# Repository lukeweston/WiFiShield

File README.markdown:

CC3000 Arduino-compatible 802.11b/g Wi-Fi shield   

Board must be fabbed with 1.6mm thick FR4 (although the microstrip impedence is not a strong function of board thickness), 2-layer 1 oz. Cu, with soldermask on both sides,
so that the 50-ohm coplanar waveguide has an impedence in the right ballpark.   
   
Preview image:   

Readme to be done later.

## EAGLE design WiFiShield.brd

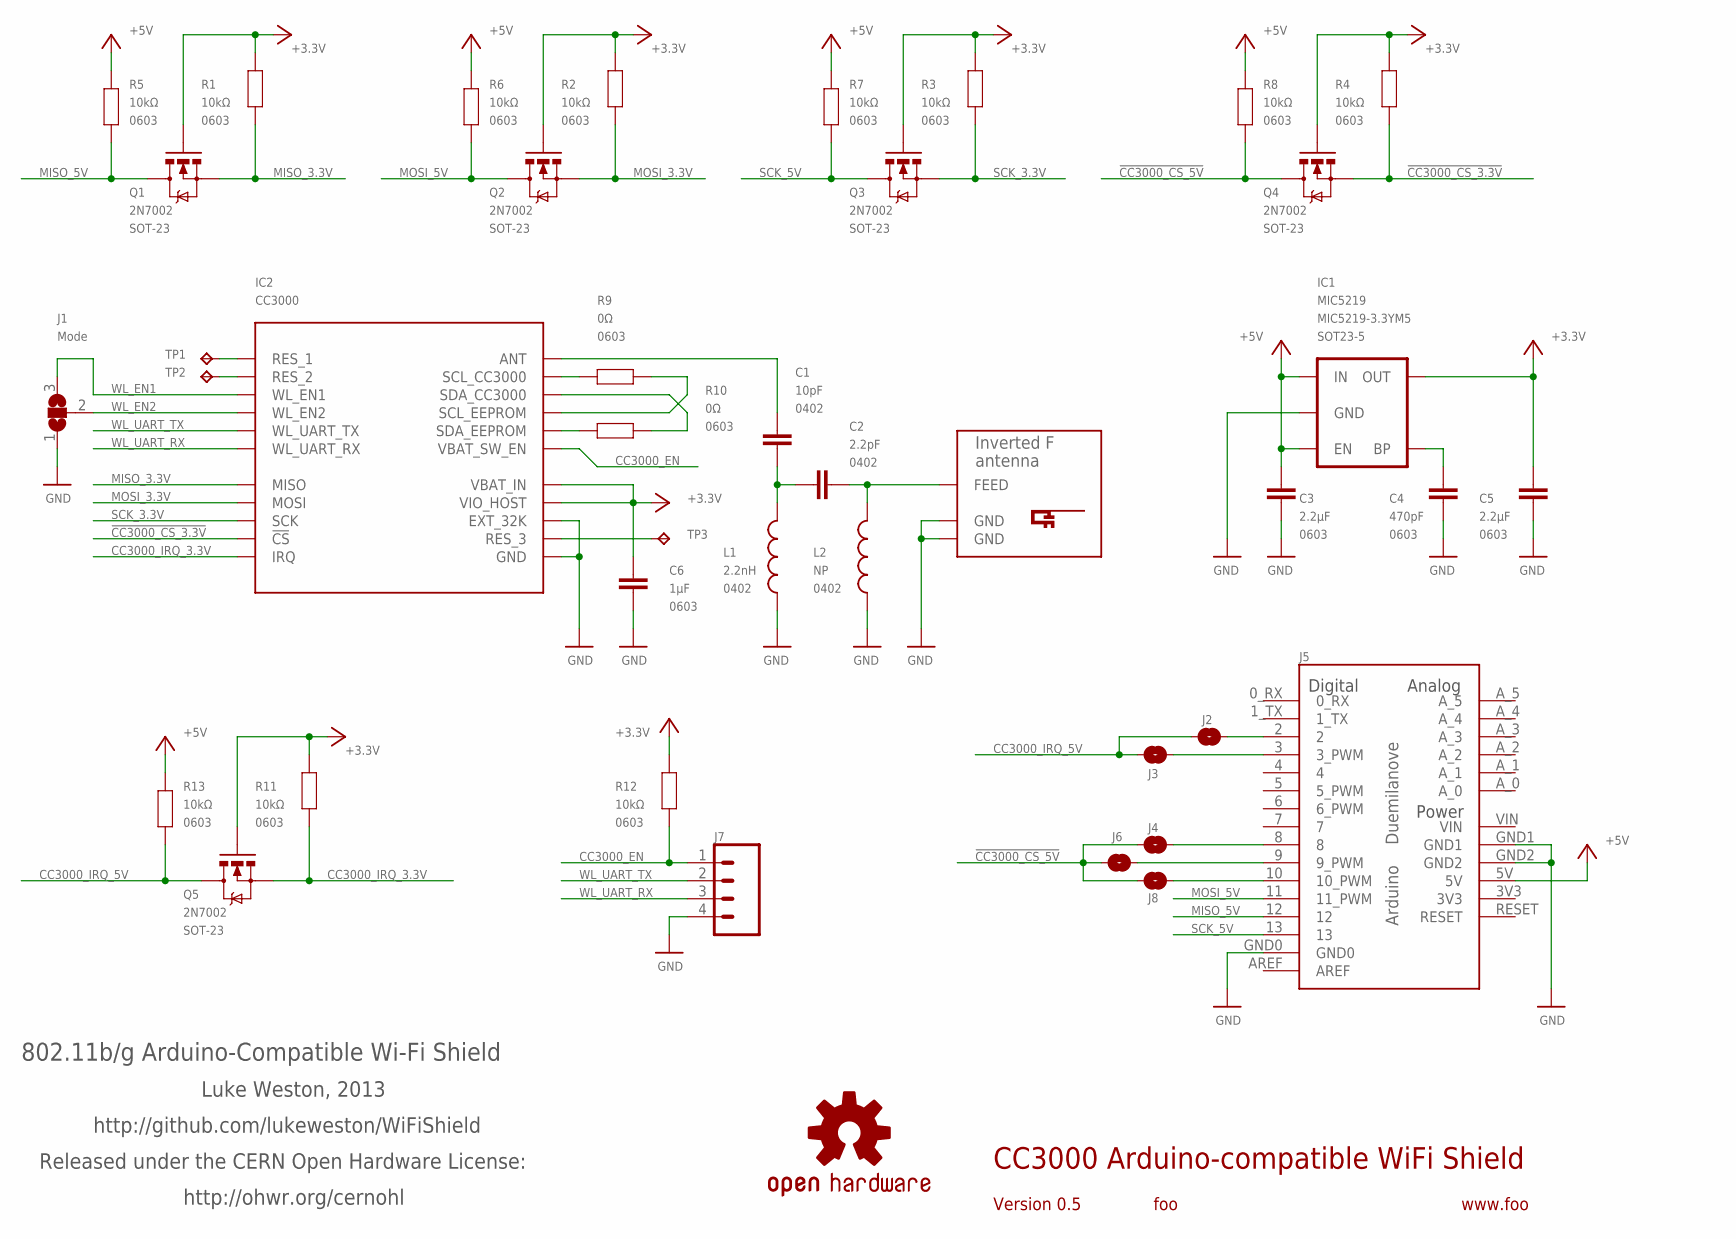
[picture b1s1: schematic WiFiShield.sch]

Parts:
A1: INVERTED_F_ANTENNA+2; DN007+2
C1: 10pF; C0402
C2: 2.2pF; C0402
C3, C5: 2.2µF; 0603
C4: 470pF; 0603
C6: 1µF; 0603
IC1: MIC5219; SOT23-5
IC2: CC3000
J1: Mode; SJ_2
J2, J3, J4, J6, J8: SJ
J5: Arduino-compatible headers; NO-OUTLINE-OCTAGONAL-NOTEXT
J7: M041.27MM; 1X04-1.27MM
L1: 2.2nH; C0402
L2: NP; C0402
Q1, Q2, Q3, Q4, Q5: 2N7002; SOT23-3
R1, R2, R3, R4, R5, R6, R7, R8, R11, R12, R13: 10kΩ; 0603
R9, R10: 0Ω; 0603
SY: OSHW-LOGOS; OSHW-LOGO-S
TP1, TP2, TP3: TPTP06R; TP06R

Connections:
3V3: J5.3V3
!CC3000_CS_3.3V: IC2.12 (!CS), Q4.2 (S), R4.1
!CC3000_CS_5V: J4.1, J6.1, J8.1, Q4.3 (D), R8.1
+3V3: C5.1, C6.2, IC1.5 (OUT), IC2.19 (VBAT_IN), IC2.23 (VIO_HOST), Q1.1 (G), Q2.1 (G), Q3.1 (G), Q4.1 (G), Q5.1 (G), R1.2, R2.2, R3.2, R4.2, R11.2, R12.2
+5V: C3.2, IC1.1 (IN), IC1.3 (EN), J5.5V, R5.2, R6.2, R7.2, R8.2, R13.2
CC3000_EN: IC2.26 (VBAT_SW_EN), J7.1, R12.1
CC3000_IRQ_3.3V: IC2.14 (IRQ), Q5.2 (S), R11.1
CC3000_IRQ_5V: J2.1, J3.1, Q5.3 (D), R13.1
GND: A1.GND, A1.GND@1 (GND), C3.1, C4.1, C5.2, C6.1, IC1.2 (GND), IC2.1 (GND), IC2.9 (GND), IC2.10 (GND), IC2.11 (GND), IC2.16 (GND), IC2.18 (GND), IC2.20 (GND), IC2.21 (EXT_32K), IC2.22 (GND), IC2.25 (GND), IC2.31 (GND), IC2.32 (GND), IC2.33 (GND), IC2.34 (GND), IC2.36 (GND), IC2.37 (GND), IC2.38 (GND), IC2.39 (GND), IC2.40 (GND), IC2.41 (GND), IC2.42 (GND), IC2.43 (GND), IC2.44 (GND), IC2.45 (GND), IC2.46 (GND), J1.1, J5.GND0, J5.GND1, J5.GND2, J7.4, L1.2, L2.2
MISO_3.3V: IC2.13 (MISO), Q1.2 (S), R1.1
MISO_5V: J5.12, Q1.3 (D), R5.1
MOSI_3.3V: IC2.15 (MOSI), Q2.2 (S), R2.1
MOSI_5V: J5.11 (11_PWM), Q2.3 (D), R6.1
unnamed: IC2.27 (SDA_EEPROM), R10.2
unnamed: IC2.28 (SDA_CC3000), R10.1
unnamed: J3.2, J5.3 (3_PWM)
unnamed: IC2.29 (SCL_EEPROM), R9.1
unnamed: J2.2, J5.2
unnamed: J5.9 (9_PWM), J6.2
unnamed: J4.2, J5.8
unnamed: J5.10 (10_PWM), J8.2
unnamed: IC2.30 (SCL_CC3000), R9.2
unnamed: C1.2, IC2.35 (ANT)
unnamed: C4.2, IC1.4 (BP)
unnamed: C1.1, C2.2, L1.1
unnamed: A1.FEED, C2.1, L2.1
RES_1: IC2.2 (RES_1), TP1.TP
RES_2: IC2.4 (RES_2), TP2.TP
RES_3: IC2.24 (RES_3), TP3.TP
SCK_3.3V: IC2.17 (SCK), Q3.2 (S), R3.1
SCK_5V: J5.13, Q3.3 (D), R7.1
VIN: J5.VIN
WL_EN1: IC2.7 (WL_EN1), J1.3
WL_EN2: IC2.5 (WL_EN2), J1.2
WL_UART_RX: IC2.8 (WL_UART_RX), J7.3
WL_UART_TX: IC2.6 (WL_UART_TX), J7.2

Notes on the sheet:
CC3000 Arduino-compatible WiFi Shield
Version 0.5
foo
www.foo
802.11b/g Arduino-Compatible Wi-Fi Shield
Luke Weston, 2013
http://github.com/lukeweston/WiFiShield
Released under the CERN Open Hardware License:
http://ohwr.org/cernohl

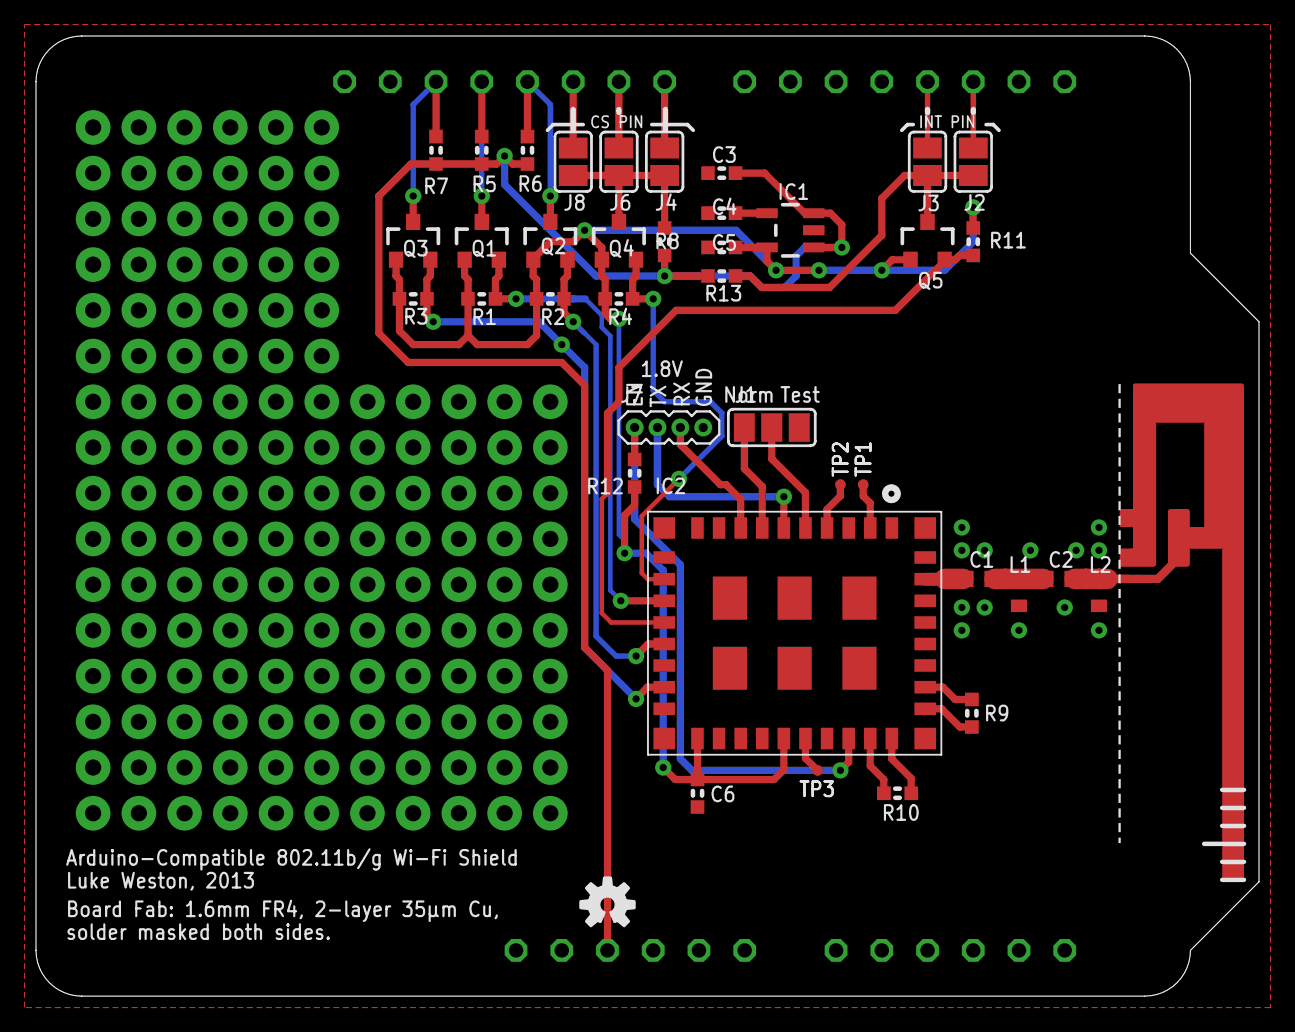
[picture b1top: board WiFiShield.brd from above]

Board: 2 copper layers, 67.9 x 53.3 mm, 41 parts (0 on the bottom side), 34 nets.

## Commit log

2013-03-17 tweaked schematic
2013-03-17 tweaked readme
2013-03-17 finished silkscreen
2013-04-06 added gerbers
2013-04-08 tweaked RF layout
2013-06-24 changed to microstrip antenna, fixed 50Ω line
2013-06-24 fixed coplanar waveguide, regenerated board image
